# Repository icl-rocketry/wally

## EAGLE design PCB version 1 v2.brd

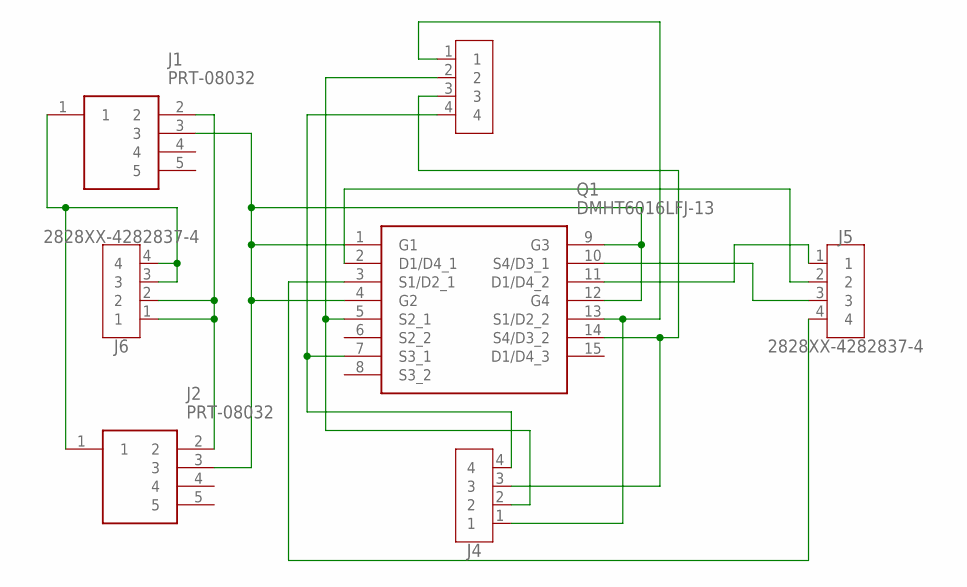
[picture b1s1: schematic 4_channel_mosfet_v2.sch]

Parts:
J1, J2: PRT-08032; PRT08032
J3, J4, J5, J6: 2828XX-4282837-4; TERMBLK_508-4N
Q1: DMHT6016LFJ-13; DMHT6016LFJ13

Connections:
unnamed: J1.1, J2.1, J6.3, J6.4
unnamed: J1.2, J2.2, J6.1, J6.2
unnamed: J1.3, J2.3, Q1.1 (G1), Q1.4 (G2), Q1.9 (G3), Q1.12 (G4)
unnamed: J3.4, J4.4, Q1.7 (S3_1)
unnamed: J3.1, J4.1, Q1.13 (S1/D2_2)
unnamed: J3.3, J4.3, Q1.14 (S4/D3_2)
unnamed: J3.2, J4.2, Q1.5 (S2_1)
unnamed: J5.3, Q1.10 (S4/D3_1)
unnamed: J5.1, Q1.11 (D1/D4_2)
unnamed: J5.2, Q1.2 (D1/D4_1)
unnamed: J5.4, Q1.3 (S1/D2_1)

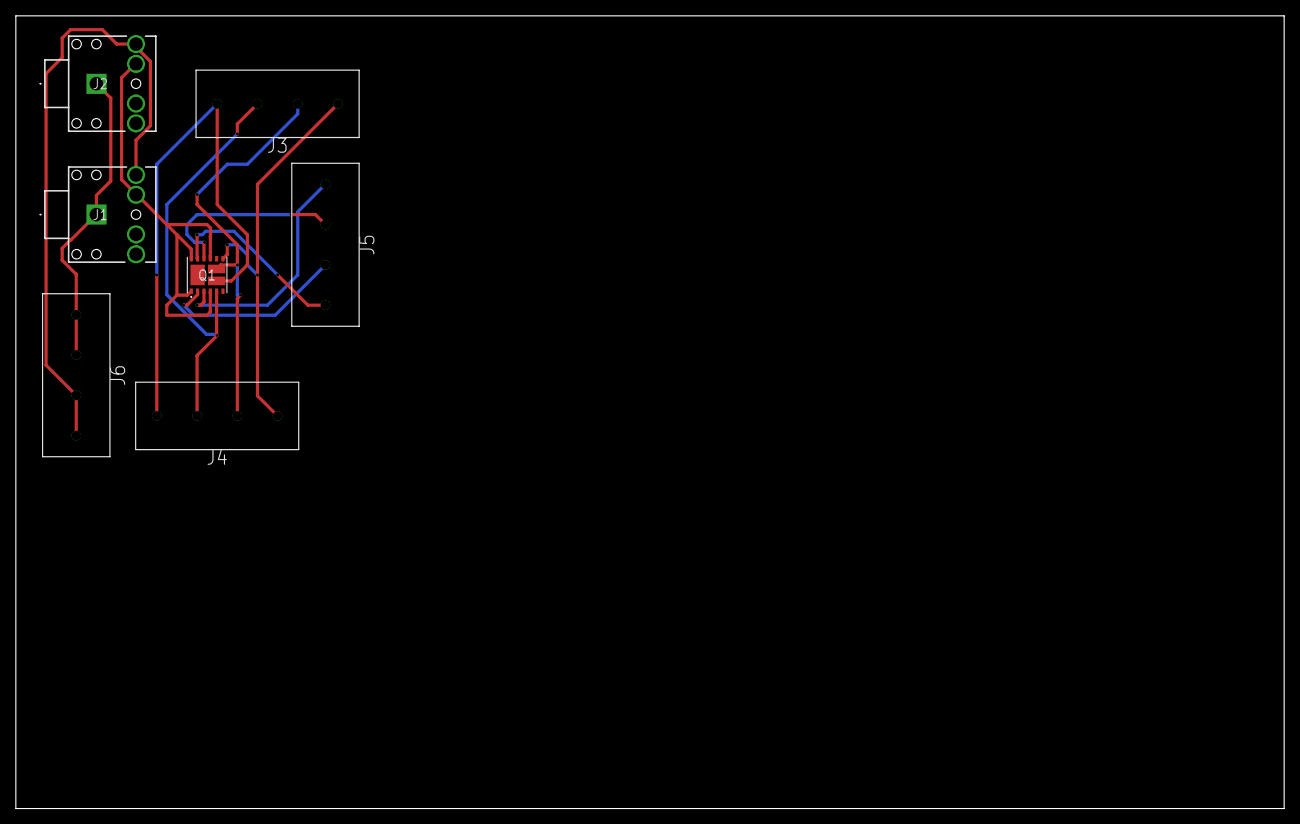
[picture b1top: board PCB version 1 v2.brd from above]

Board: 2 copper layers, 160.0 x 100.0 mm, 7 parts (0 on the bottom side), 11 nets.

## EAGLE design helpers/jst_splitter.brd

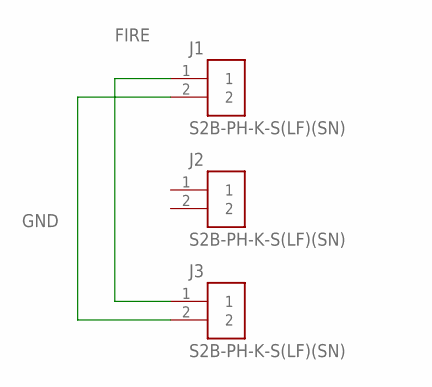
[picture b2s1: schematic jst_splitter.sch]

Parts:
J1, J2, J3: S2B-PH-K-S(LF)(SN)

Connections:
GND: J1.1, J2.1, J3.1
VCC: J1.2, J2.2, J3.2

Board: 2 copper layers, 3 parts (0 on the bottom side), 2 nets, no tracks yet.

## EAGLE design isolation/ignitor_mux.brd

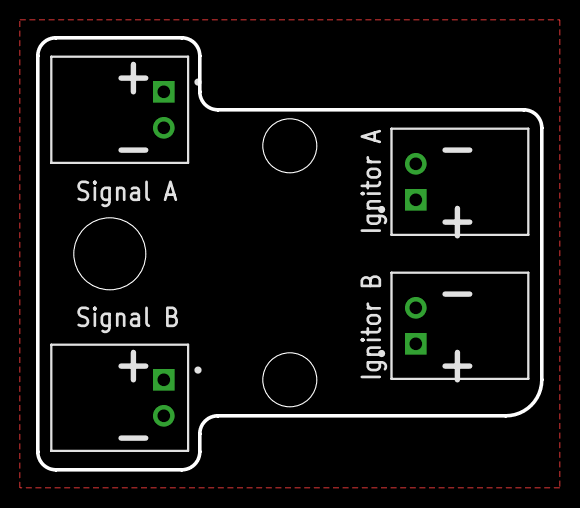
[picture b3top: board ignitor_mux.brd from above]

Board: 2 copper layers, 28.0 x 24.0 mm, 4 parts (0 on the bottom side), 2 nets, no tracks yet.

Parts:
J1, J2, J3, J4: S2B-PH-K-S(LF)(SN)

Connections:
FIRE: J1.1, J2.1, J3.1, J4.1
GND: J1.2, J2.2, J3.2, J4.2

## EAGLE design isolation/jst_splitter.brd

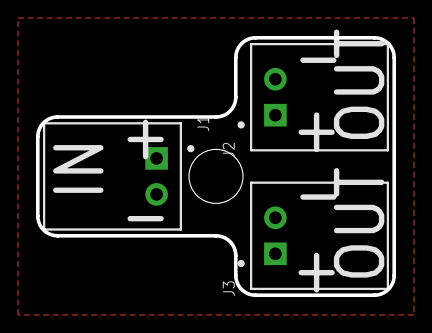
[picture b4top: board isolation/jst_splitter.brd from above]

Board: 2 copper layers, 19.8 x 14.3 mm, 3 parts (0 on the bottom side), 2 nets, no tracks yet.

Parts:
J1, J2, J3: S2B-PH-K-S(LF)(SN)

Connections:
FIRE: J1.1, J3.1
GND: J1.2, J3.2

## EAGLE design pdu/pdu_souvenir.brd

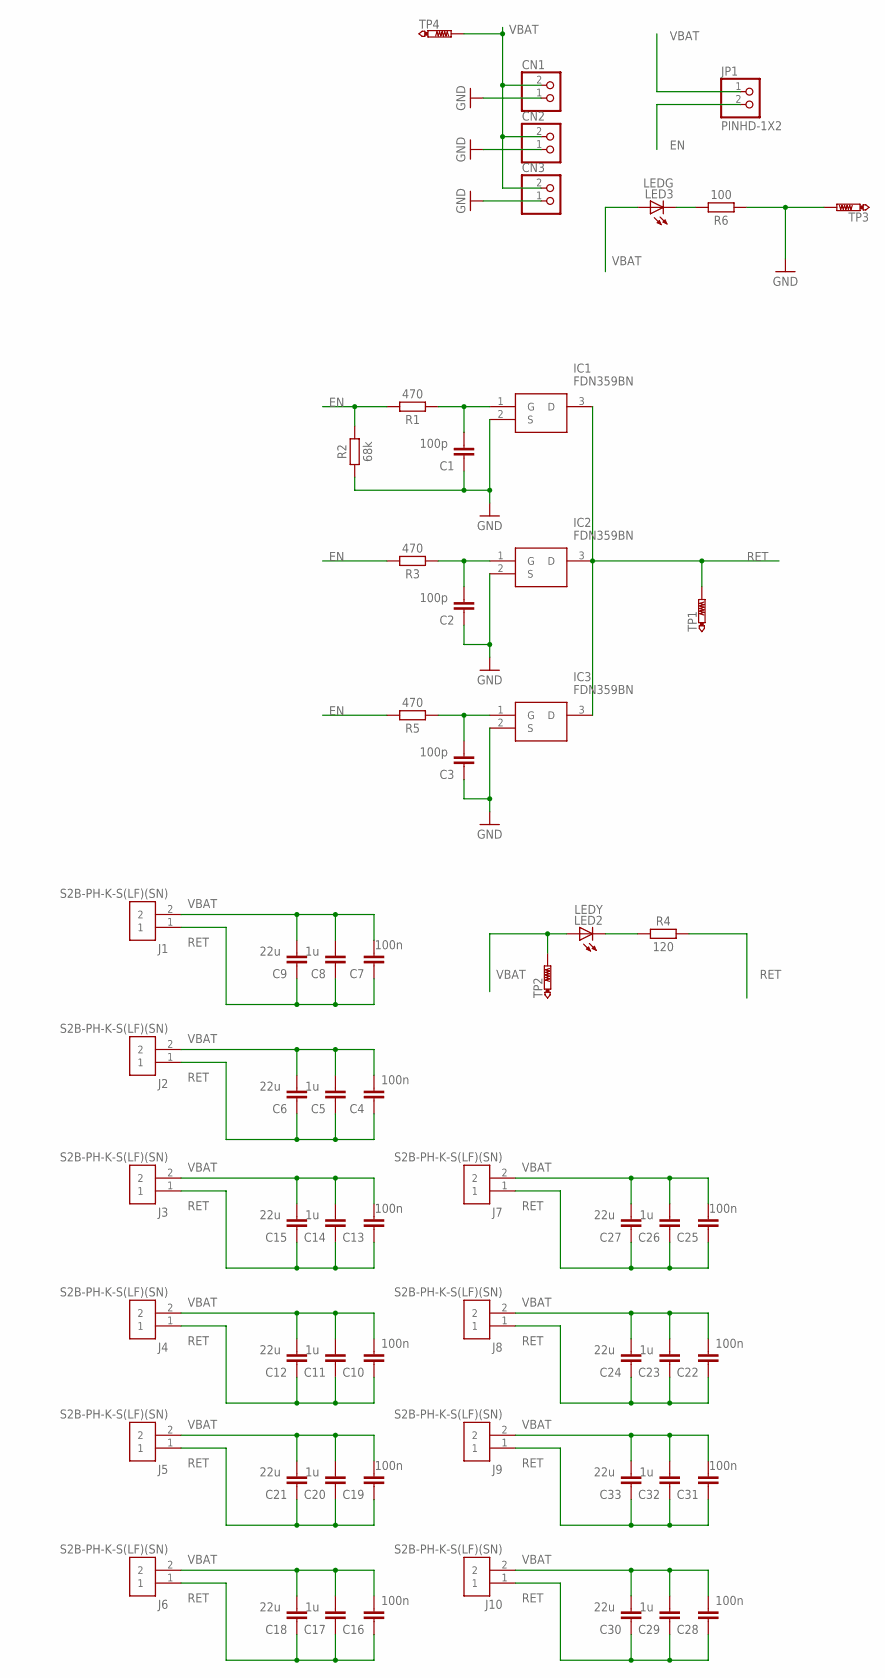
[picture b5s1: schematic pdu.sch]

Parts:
C1, C2, C3: 100p; CAPC1608X85
C4, C7, C10, C13, C16, C19, C22, C25, C28, C31: 100n; CAPC1608X85
C5, C8, C11, C14, C17, C20, C23, C26, C29, C32: 1u; CAPC1608X85
C6, C9, C12, C15, C18, C21, C24, C27, C30, C33: 22u; CAPC1608X85
CN1, CN2, CN3: JST_2PIN-THM-RA; JST-PH-2-THM-RA
IC1, IC2, IC3: FDN359BN; SOT95P251X112-3N
J1, J2, J3, J4, J5, J6, J7, J8, J9, J10: S2B-PH-K-S(LF)(SN)
JP1: PINHD-1X2; 1X02
LED2: LEDY; CHIPLED_0805
LED3: LEDG; CHIPLED_0805
R1, R3, R5: 470; RESC1608X60
R2: 68k; RESC1608X60
R4: 120; RESC1608X60
R6: 100; RESC1608X60
TP1, TP2, TP3, TP4: PTR1PAD1-13; P1-13

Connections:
EN: JP1.2, R1.2, R2.2, R3.2, R5.2
GND: C1.1, C2.1, C3.1, CN1.1 (2), CN2.1 (2), CN3.1 (2), IC1.2 (S), IC2.2 (S), IC3.2 (S), R2.1, R6.1, TP3.TP; also elsewhere on the board
unnamed 2: C1.2, IC1.1 (G), R1.1; also elsewhere on the board
unnamed: C2.2, IC2.1 (G), R3.1
unnamed: C3.2, IC3.1 (G), R5.1
unnamed: LED3.C, R6.2
unnamed: LED2.C, R4.1
RET: C4.1, C5.1, C6.1, C7.1, C8.1, C9.1, C10.1, C11.1, C12.1, C13.1, C14.1, C15.1, C16.1, C17.1, C18.1, C19.1, C20.1, C21.1, C22.1, C23.1, C24.1, C25.1, C26.1, C27.1, C28.1, C29.1, C30.1, C31.1, C32.1, C33.1, IC1.3 (D), IC2.3 (D), IC3.3 (D), J1.1, J2.1, J3.1, J4.1, J5.1, J6.1, J7.1, J8.1, J9.1, J10.1, R4.2, TP1.TP; also elsewhere on the board
VBAT: C4.2, C5.2, C6.2, C7.2, C8.2, C9.2, C10.2, C11.2, C12.2, C13.2, C14.2, C15.2, C16.2, C17.2, C18.2, C19.2, C20.2, C21.2, C22.2, C23.2, C24.2, C25.2, C26.2, C27.2, C28.2, C29.2, C30.2, C31.2, C32.2, C33.2, CN1.2 (1), CN2.2 (1), CN3.2 (1), J1.2, J2.2, J3.2, J4.2, J5.2, J6.2, J7.2, J8.2, J9.2, J10.2, JP1.1, LED2.A, LED3.A, TP2.TP, TP4.TP

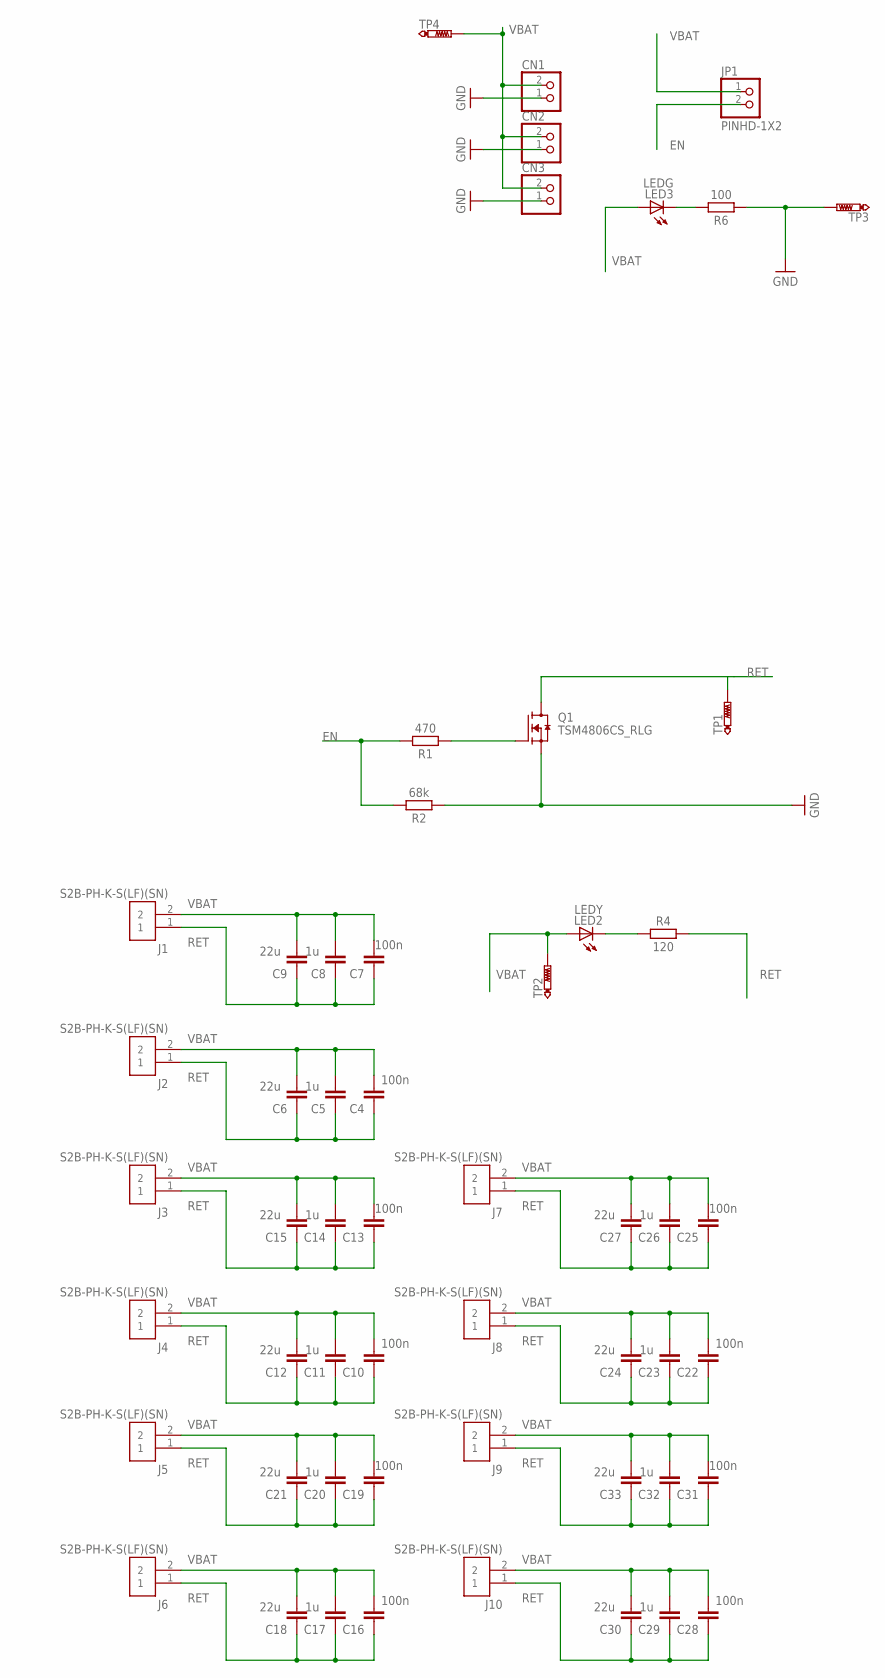
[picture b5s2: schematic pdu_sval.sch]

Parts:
C4, C7, C10, C13, C16, C19, C22, C25, C28, C31: 100n; CAPC1608X85
C5, C8, C11, C14, C17, C20, C23, C26, C29, C32: 1u; CAPC1608X85
C6, C9, C12, C15, C18, C21, C24, C27, C30, C33: 22u; CAPC1608X85
CN1, CN2, CN3: JST_2PIN-THM-RA; JST-PH-2-THM-RA
J1, J2, J3, J4, J5, J6, J7, J8, J9, J10: S2B-PH-K-S(LF)(SN)
JP1: PINHD-1X2; 1X02
LED2: LEDY; CHIPLED_0805
LED3: LEDG; CHIPLED_0805
Q1: TSM4806CS_RLG; SOP127P600X200-8N
R1: 470; RESC1608X60
R2: 68k; RESC1608X60
R4: 120; RESC1608X60
R6: 100; RESC1608X60
TP1, TP2, TP3, TP4: PTR1PAD1-13; P1-13

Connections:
EN: JP1.2, R1.2, R2.2; also elsewhere on the board
GND: CN1.1 (2), CN2.1 (2), CN3.1 (2), Q1.1 (S), R2.1, R6.1, TP3.TP; also elsewhere on the board
unnamed 2: Q1.4 (G), R1.1; also elsewhere on the board
unnamed: LED3.C, R6.2
unnamed: LED2.C, R4.1
RET: C4.1, C5.1, C6.1, C7.1, C8.1, C9.1, C10.1, C11.1, C12.1, C13.1, C14.1, C15.1, C16.1, C17.1, C18.1, C19.1, C20.1, C21.1, C22.1, C23.1, C24.1, C25.1, C26.1, C27.1, C28.1, C29.1, C30.1, C31.1, C32.1, C33.1, J1.1, J2.1, J3.1, J4.1, J5.1, J6.1, J7.1, J8.1, J9.1, J10.1, Q1.5 (D), R4.2, TP1.TP; also elsewhere on the board
VBAT: C4.2, C5.2, C6.2, C7.2, C8.2, C9.2, C10.2, C11.2, C12.2, C13.2, C14.2, C15.2, C16.2, C17.2, C18.2, C19.2, C20.2, C21.2, C22.2, C23.2, C24.2, C25.2, C26.2, C27.2, C28.2, C29.2, C30.2, C31.2, C32.2, C33.2, CN1.2 (1), CN2.2 (1), CN3.2 (1), J1.2, J2.2, J3.2, J4.2, J5.2, J6.2, J7.2, J8.2, J9.2, J10.2, JP1.1, LED2.A, LED3.A, TP2.TP, TP4.TP

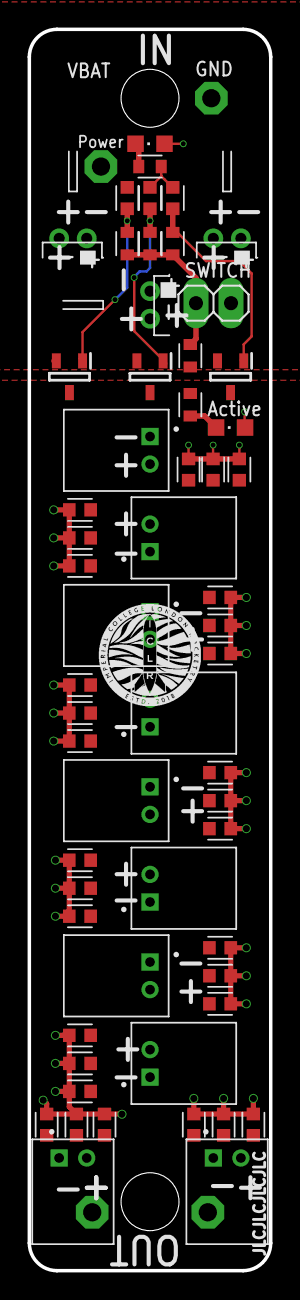
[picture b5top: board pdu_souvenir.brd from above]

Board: 2 copper layers, 17.5 x 90.0 mm, 62 parts (0 on the bottom side), 9 nets.

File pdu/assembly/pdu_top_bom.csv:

Comment,Designator,Footprint,LCSC Part #
1u,C5 C8 C11 C14 C17 C20 C23 C26 C29 C32,CAPC1608X85,C15849
22u,C6 C9 C12 C15 C18 C21 C24 C27 C30 C33,CAPC1608X85,C59461
68k,R2,RESC1608X60,C23231
100,R6,RESC1608X60,C22775
100n,C4 C7 C10 C13 C16 C19 C22 C25 C28 C31,CAPC1608X85,C14663
100p,C1 C2 C3,CAPC1608X85,C14858
120,R4,RESC1608X60,C22787
470,R1 R3 R5,RESC1608X60,C23179
FDN359BN,IC1 IC2 IC3,SOT95P251X112-3N,C5290365
LEDG,LED3,CHIPLED_0805,C2297
LEDY,LED2,CHIPLED_0805,C2296
